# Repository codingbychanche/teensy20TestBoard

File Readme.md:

A general purpose PCB for the Teensy 2.0 MCU

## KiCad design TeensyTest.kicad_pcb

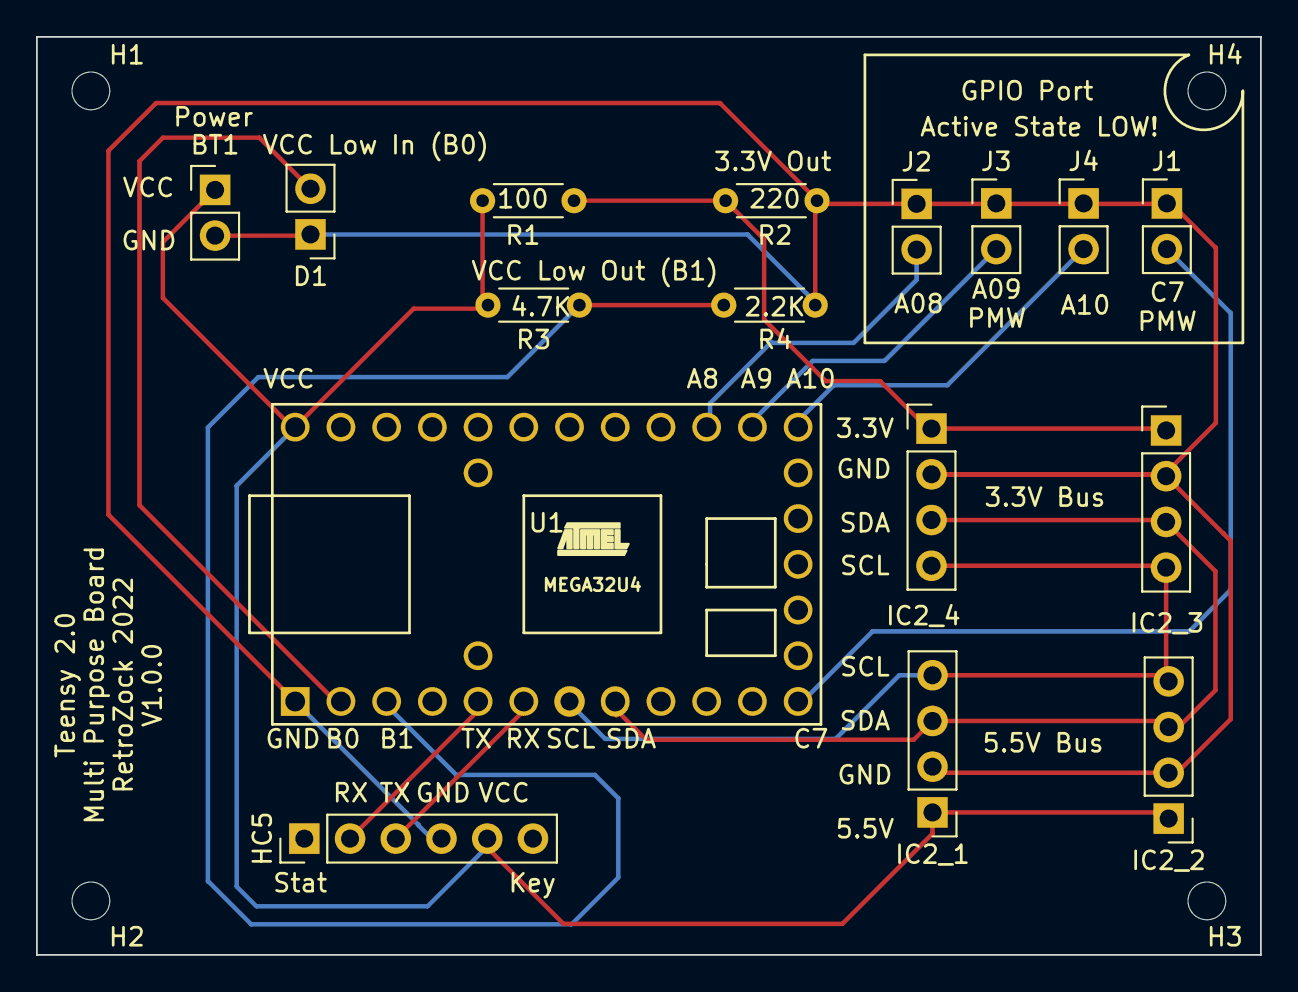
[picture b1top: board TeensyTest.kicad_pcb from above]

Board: 2 copper layers, 68.0 x 51.0 mm, 20 parts (0 on the bottom side), 6 nets.

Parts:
BT1: Battery; PinHeader_1x02_P2.54mm_Vertical
D1: LED; PinHeader_1x02_P2.54mm_Vertical
H1, H2, H3, H4: MountingHole; MountingHole_2.1mm
HC5: Conn_01x06_Female; PinHeader_1x06_P2.54mm_Vertical
IC2_1, IC2_2, IC2_3, IC2_4: Conn_01x04_Female; PinHeader_1x04_P2.54mm_Vertical
J1, J2, J3, J4: Conn_01x02_Female; PinHeader_1x02_P2.54mm_Vertical
R1: 100; R_Axial_DIN0204_L3.6mm_D1.6mm_P5.08mm_Horizontal
R2: 220; R_Axial_DIN0204_L3.6mm_D1.6mm_P5.08mm_Horizontal
R3: 4.7K; R_Axial_DIN0204_L3.6mm_D1.6mm_P5.08mm_Horizontal
R4: 2.2K; R_Axial_DIN0204_L3.6mm_D1.6mm_P5.08mm_Horizontal
U1: Teensy2.0_(Arduino); Teensy2.0

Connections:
/3.3V: IC2_3.1, IC2_4.1, R2.2
/5.5V: BT1.1 (+), HC5.5, IC2_1.1, IC2_2.1, R3.2
/GND: BT1.2 (-), D1.1 (K), HC5.4, IC2_1.2, IC2_2.2, IC2_3.2, IC2_4.2, J1.1, J2.1, J3.1, J4.1, R2.1, R4.1
/SCL: IC2_1.4, IC2_2.4, IC2_3.4, IC2_4.4
/SDA: IC2_1.3, IC2_2.3, IC2_3.3, IC2_4.3
/VCC_LOW: R3.1, R4.2

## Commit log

2022-01-07 A general purpose pcb for Teensy 2.0
2022-01-07 Added
